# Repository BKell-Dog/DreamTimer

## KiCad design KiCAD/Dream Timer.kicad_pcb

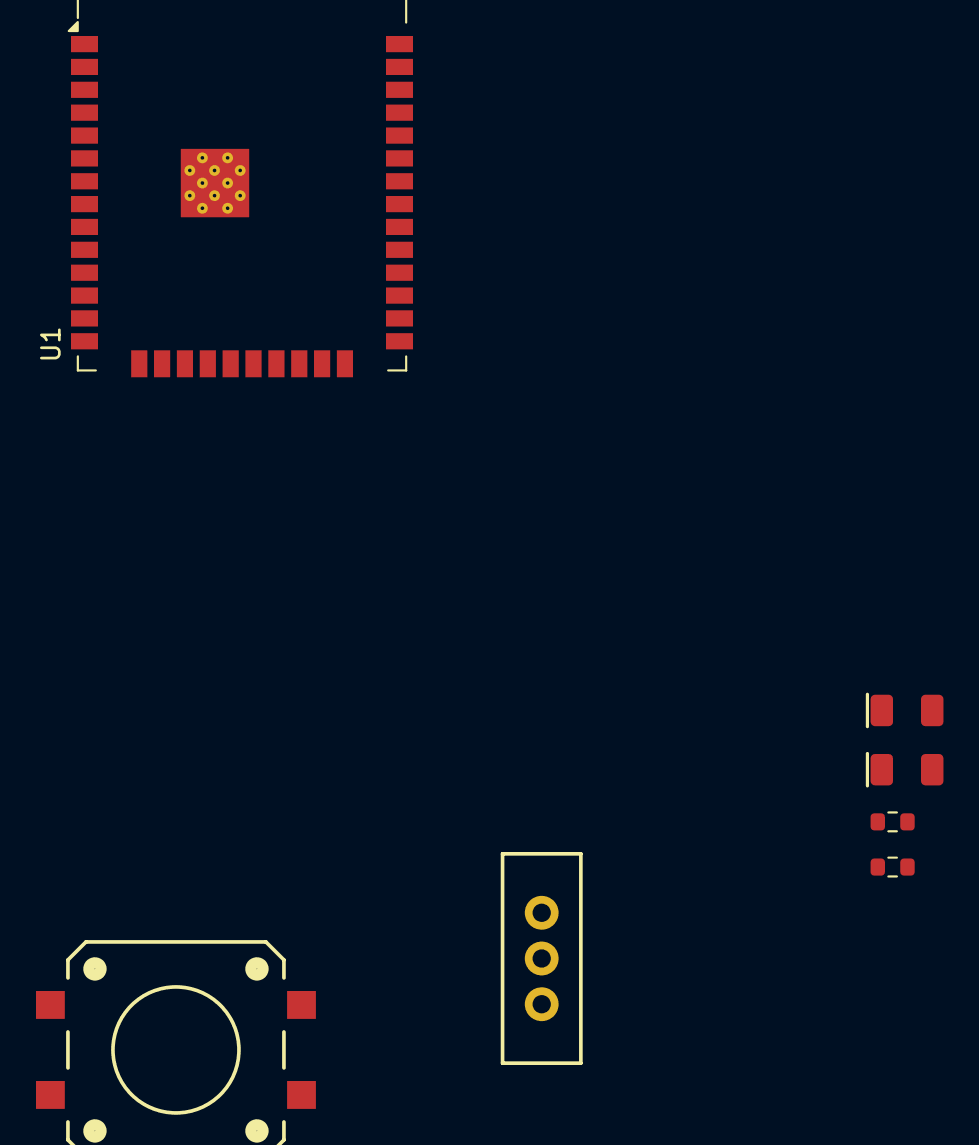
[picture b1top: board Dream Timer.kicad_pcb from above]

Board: 2 copper layers, 7 parts (0 on the bottom side), 8 nets, no tracks yet.

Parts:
D1: Blue; LED_1206_3216Metric_Blue
D2: Yellow; LED_1206_3216Metric_Yellow
R1, R2: 470; R_0603_1608Metric
SW1_State_Toggle1: SMD_12x12mm_h8.5mm; Push_SMD_12x12mm
SW2_Mode_Toggle1: SPDT_Slide_PTH_11.6x4.0mm; Slide_SPDT_PTH_11.6x4.0mm
U1: ESP32-WROOM-32D

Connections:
GND: R1.2, R2.2, SW1_State_Toggle1.2, SW2_Mode_Toggle1.3 (C), U1.1 (GND), U1.15 (GND), U1.38 (GND), U1.39 (GND)
unnamed: D1.2 (A), U1.27 (IO16)
unnamed: D1.1 (K), R1.1
unnamed: D2.2 (A), U1.28 (IO17)
unnamed: D2.1 (K), R2.1
unnamed: SW2_Mode_Toggle1.2 (B), U1.33 (IO21)
unnamed: SW1_State_Toggle1.1, U1.37 (IO23)
VCC: SW2_Mode_Toggle1.1 (A), U1.2 (VDD)

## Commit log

2026-02-06 Initial commit.
    Initial commit after some significant development. Had Claude write some code, separate them into local libraries. Got a working prototype up.
2026-02-06 Include KiCAD files, and small improvements on the code.
2026-02-06 Restructure files and add README with mermaid diagram.
2026-02-06 Update README.
2026-02-15 Massive Reduction in Complexity.
    Claude pumped out code too fast and made spaghetti. I wanted modularity, but he didn't do it right. Now I've removed certain functionality to simplify the project again, and made it modular, and now 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
2026-02-16 Working CLOCK mode.
2026-02-25 Add working EEPROM Helper class to read/write from EEPROM.
    EEPROM Helper works as intended, but now if Wifi is disconnected, CLOCK mode does not count up smoothly anymore, but rather counts in fits and starts.
2026-02-26 Remove blocking WIFI, just connect async in the background.
2026-03-16 Fix timer lag issue when switching from Sleep -> Wake or vice versa.
